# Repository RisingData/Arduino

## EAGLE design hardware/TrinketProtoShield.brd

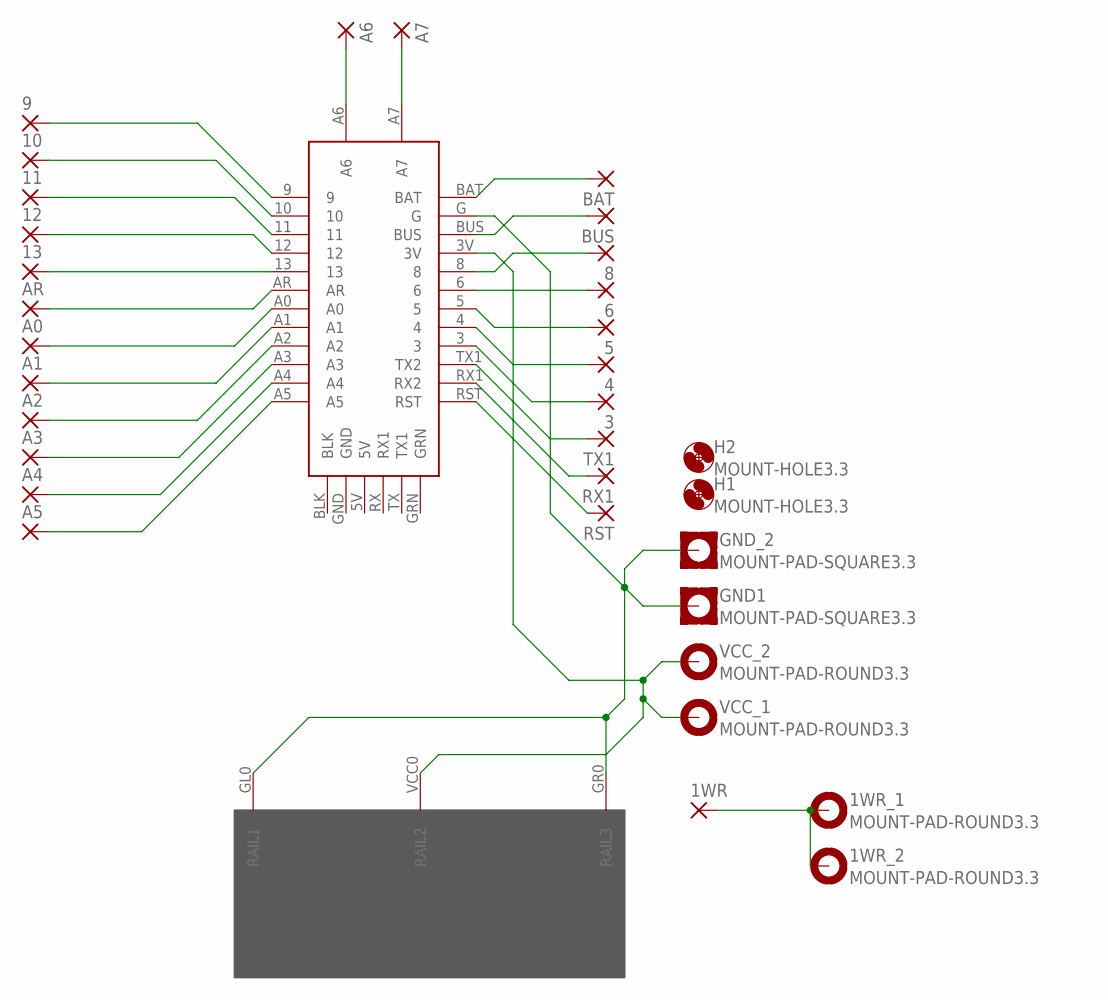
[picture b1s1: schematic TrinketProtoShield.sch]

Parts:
1WR, 3, 4, 5, 6, 8, 9, 10, 11, 12, 13: 1,6/0,9
1WR_1, 1WR_2: MOUNT-PAD-ROUND3.3; 3,3-PAD
A0, A1, A2, A3, A4, A5, A6, A7: 1,6/0,9
AR: 1,6/0,9
BAT: 1,6/0,9
BUS: 1,6/0,9
GND1: MOUNT-PAD-SQUARE3.3; 3,3-PAD-SQUARE
GND_2: MOUNT-PAD-SQUARE3.3; 3,3-PAD-SQUARE
H1, H2: MOUNT-HOLE3.3; 3,3
RST: 1,6/0,9
RX1: 1,6/0,9
TX1: 1,6/0,9
U$1: ARDUINO_PRO_TRINKET
U$2: PROTOAREA
VCC_1, VCC_2: MOUNT-PAD-ROUND3.3; 3,3-PAD

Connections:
unnamed: 9.1, U$1.9
unnamed: 10.1, U$1.10
unnamed: 11.1, U$1.11
unnamed: 12.1, U$1.12
unnamed: 13.1, U$1.13
unnamed: AR.1, U$1.AR
unnamed: A0.1, U$1.A0
unnamed: A1.1, U$1.A1
unnamed: A2.1, U$1.A2
unnamed: A3.1, U$1.A3
unnamed: A4.1, U$1.A4
unnamed: A5.1, U$1.A5
unnamed: A6.1, U$1.A6
unnamed: A7.1, U$1.A7
unnamed: BAT.1, U$1.BAT
unnamed: BUS.1, U$1.BUS
unnamed: 8.1, U$1.8
unnamed: 6.1, U$1.6
unnamed: 1WR.1, 1WR_1.B3,3, 1WR_2.B3,3
unnamed: 5.1, U$1.5
unnamed: 4.1, U$1.4
unnamed: 3.1, U$1.3
unnamed: TX1.1, U$1.TX1 (TX2)
unnamed: RX1.1, U$1.RX1 (RX2)
unnamed: RST.1, U$1.RST
unnamed: GND1.B3,3, GND_2.B3,3, U$1.G, U$2.GL0 (RAIL1), U$2.GR0 (RAIL3)
unnamed: U$1.3V, U$2.VCC0 (RAIL2), VCC_1.B3,3, VCC_2.B3,3

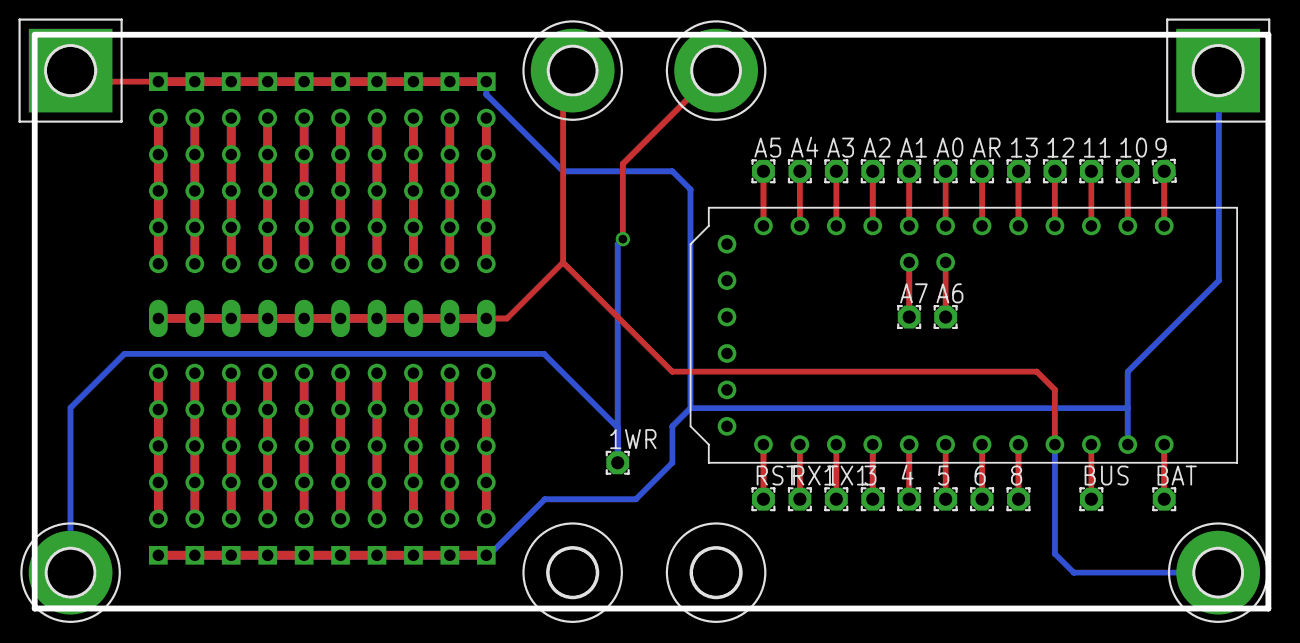
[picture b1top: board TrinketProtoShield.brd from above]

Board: 2 copper layers, 86.0 x 40.0 mm, 35 parts (0 on the bottom side), 27 nets.

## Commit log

2016-10-17 added initial documents and code to write to SD card
2016-10-17 added libraries for SD card and 9DOF, integrated both libaries into flight code for Rising Data.
2016-10-17 added hardware source files and a component reference guide
2016-10-18 added some doc images and sample data
2016-10-18 finished Arduino IDE Setup Guide, made wiring diagrams, started the SD card intergration docs
2016-10-19 write integration guide for SD card
2016-10-19 refactored 9DOF example code and wrote integration guide for 9Dof sensor
2016-10-19 moved image documentation from adafruit into a sub folder. Cleaned up the flight code just a bit
2016-10-19 added simple sketches for TMP-36 and LED
2016-10-19 corrected images of APT 5V to APT 3V
2016-10-19 added documentation for TMP-36
